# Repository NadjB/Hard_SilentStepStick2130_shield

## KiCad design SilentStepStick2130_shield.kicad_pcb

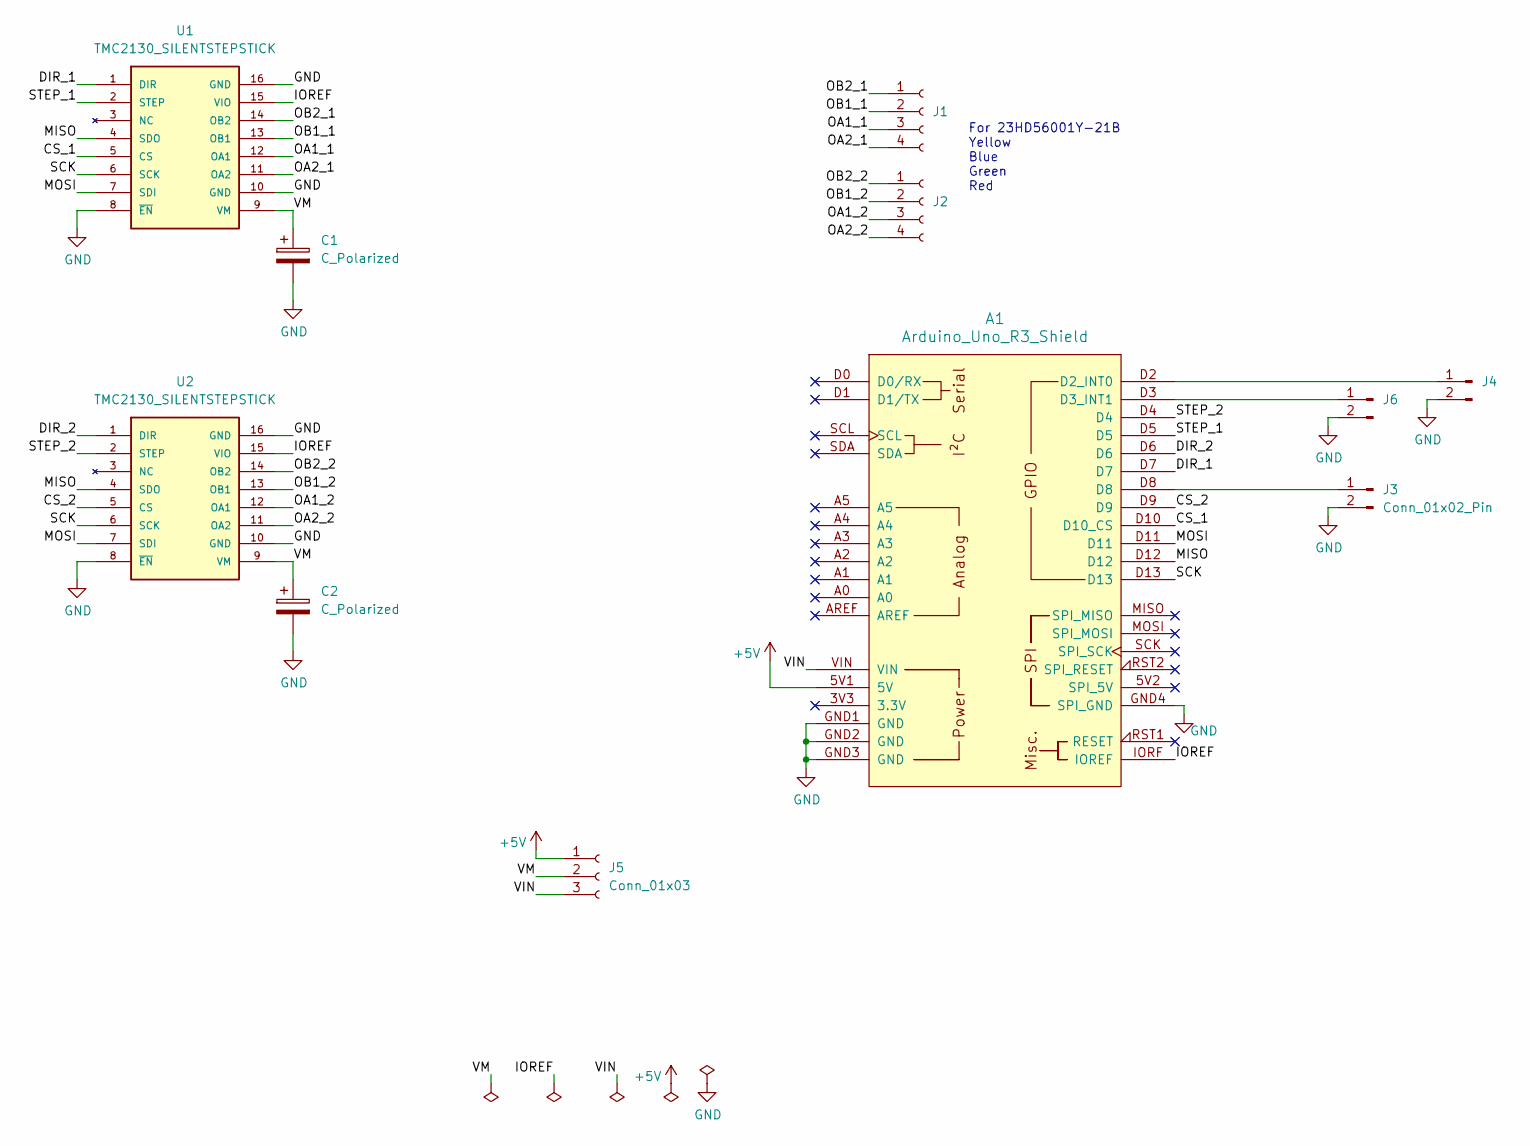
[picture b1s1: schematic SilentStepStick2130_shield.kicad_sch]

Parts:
A1: Arduino_Uno_R3_Shield
C1, C2: C_Polarized; CP_EIA-7343-43_Kemet-X_Pad2.25x2.55mm_HandSolder
J1, J2: Conn_01x04_Socket; CUI_TBL009-254-04BK-2OR
J3, J4, J6: Conn_01x02_Pin; JST_XA_S02B-XASK-1_1x02_P2.50mm_Horizontal
J5: Conn_01x03; PinHeader_1x03_P2.54mm_Vertical; Part Number 1-0301FBV0T
U1, U2: TMC2130_SILENTSTEPSTICK

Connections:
+5V: A1.5V1 (5V), J5.1
/CS_1: A1.D10 (D10_CS), U1.5 (CS)
/CS_2: A1.D9, U2.5 (CS)
/DIR_1: A1.D7, U1.1 (DIR)
/DIR_2: A1.D6, U2.1 (DIR)
/IOREF: A1.IORF (IOREF), U1.15 (VIO), U2.15 (VIO)
/MISO: A1.D12, U1.4 (SDO), U2.4 (SDO)
/MOSI: A1.D11, U1.7 (SDI), U2.7 (SDI)
/OA1_1: J1.3, U1.12 (OA1)
/OA1_2: J2.3, U2.12 (OA1)
/OA2_1: J1.4, U1.11 (OA2)
/OA2_2: J2.4, U2.11 (OA2)
/OB1_1: J1.2, U1.13 (OB1)
/OB1_2: J2.2, U2.13 (OB1)
/OB2_1: J1.1, U1.14 (OB2)
/OB2_2: J2.1, U2.14 (OB2)
/SCK: A1.D13, U1.6 (SCK), U2.6 (SCK)
/STEP_1: A1.D5, U1.2 (STEP)
/STEP_2: A1.D4, U2.2 (STEP)
/VIN: A1.VIN, J5.3
/VM: C1.1, C2.1, J5.2, U1.9 (VM), U2.9 (VM)
GND: A1.GND1 (GND), A1.GND2 (GND), A1.GND3 (GND), A1.GND4 (SPI_GND), C1.2, C2.2, J3.2, J4.2, J6.2, U1.8 (~EN), U1.10 (GND), U1.16 (GND), U2.8 (~EN), U2.10 (GND), U2.16 (GND)
unnamed: A1.D2 (D2_INT0), J4.1
unnamed: A1.D3 (D3_INT1), J6.1
unnamed: A1.D8, J3.1

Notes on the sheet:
For 23HD56001Y-21B Yellow Blue Green Red

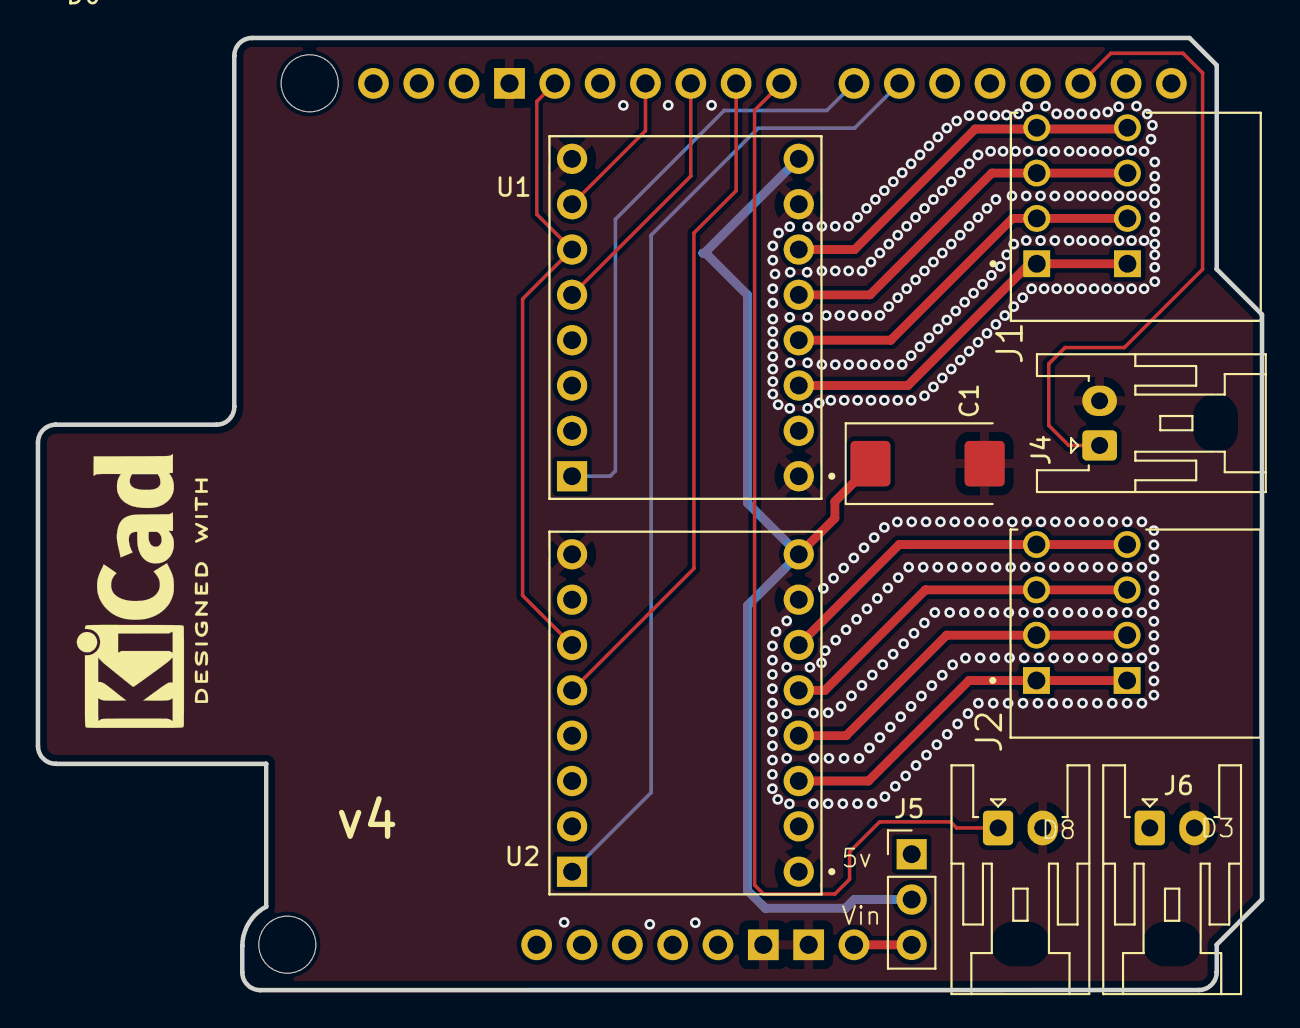
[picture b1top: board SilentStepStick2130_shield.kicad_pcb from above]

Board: 4 copper layers, 68.6 x 53.3 mm, 11 parts (1 on the bottom side), 25 nets.

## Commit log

2024-03-15 v0 sent to fab
2024-05-27 Changed to the new arduino symbol and moved the chipSelect from 11 12 to 12 13 Hard set enables to GND to get 3 digital input free for endcourse contacts Fliped the TMC2130 so that their backside fac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
2024-11-29 modified shield footprint to reconnect 5v and gnd.kicad_pcb
2025-03-20 Changed connectors for end course
